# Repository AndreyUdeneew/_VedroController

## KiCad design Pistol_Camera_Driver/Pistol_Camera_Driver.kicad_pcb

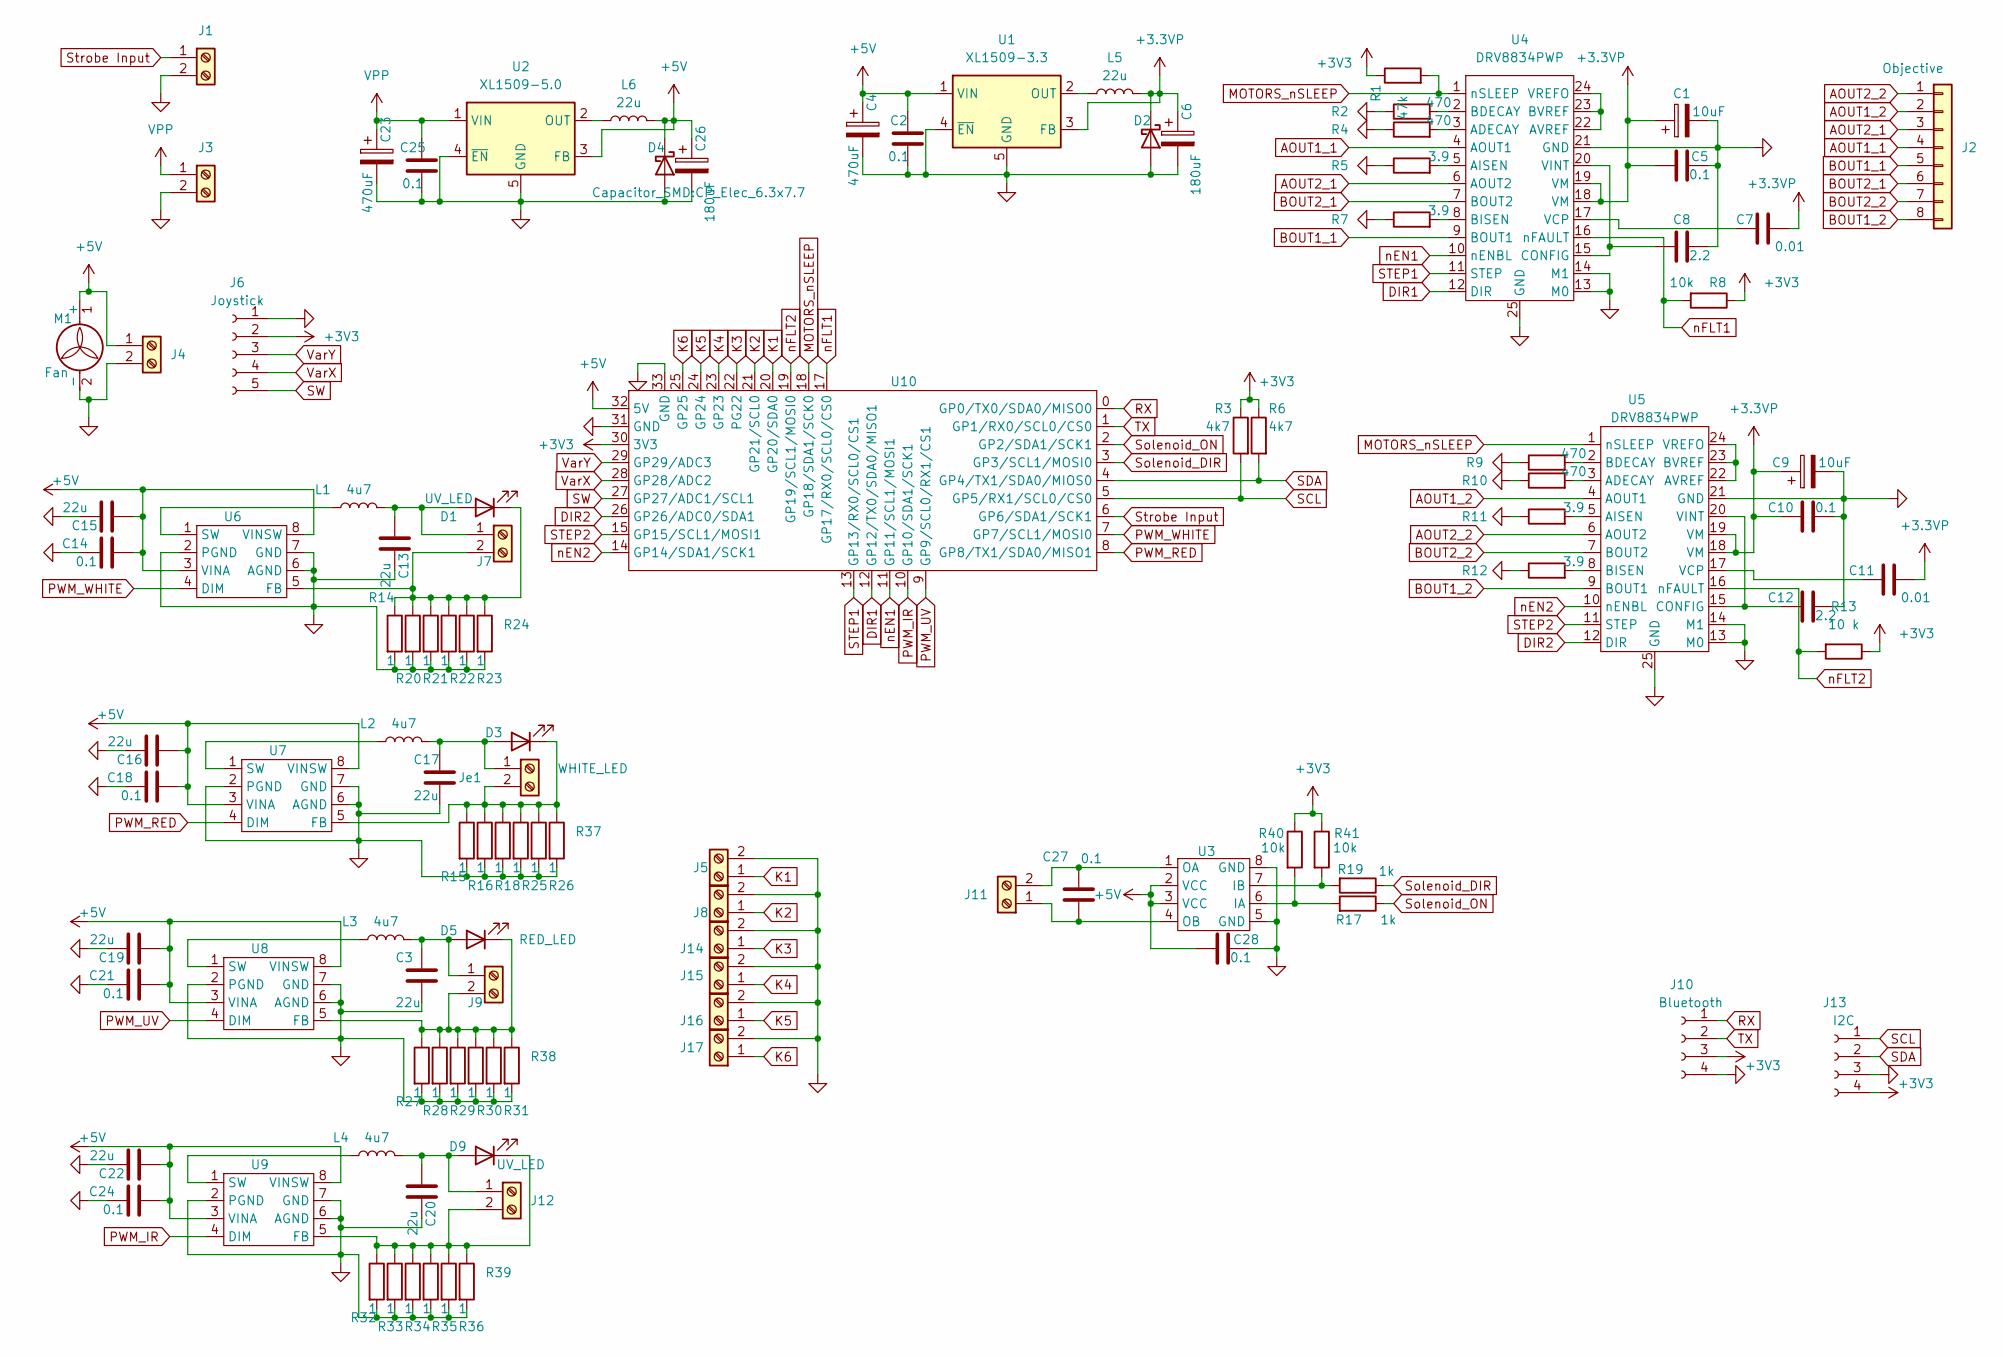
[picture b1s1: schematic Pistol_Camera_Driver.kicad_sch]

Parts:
C1, C9: 10uF; CP_Radial_D6.3mm_P2.50mm
C2, C5, C10, C14, C18, C21, C24, C25, C27, C28: 0.1; C_0603_1608Metric_Pad1.08x0.95mm_HandSolder
C3, C13, C15, C16, C17, C19, C20, C22: 22u; C_0603_1608Metric_Pad1.08x0.95mm_HandSolder
C4, C23: 470uF; CP_Elec_10x10.5
C6, C26: 180uF; CP_Elec_6.3x7.7
C7, C11: 0.01; C_0603_1608Metric_Pad1.08x0.95mm_HandSolder
C8, C12: 2.2; C_0603_1608Metric_Pad1.08x0.95mm_HandSolder
D1, D9: UV_LED
D2, D4: CDBA3100-HF; D_SMA
D3: WHITE_LED
D5: RED_LED
J1, J3, J4, J5, J7, J8, J9, J12, J14, J15, J16, J17: Screw_Terminal_01x02; PinSocket_1x02_P2.54mm_Vertical
J2: Objective; PinSocket_1x08_P1.27mm_Vertical
J6: Joystick; PinSocket_1x05_P2.54mm_Vertical
J10: Bluetooth; PinSocket_1x04_P2.54mm_Vertical
J11: Screw_Terminal_01x02; PinSocket_1x02_P1.27mm_Vertical
J13: I2C; PinSocket_1x04_P2.54mm_Vertical
Je1: Screw_Terminal_01x02; PinSocket_1x02_P2.54mm_Vertical
L1, L2, L3, L4: 4u7; L_Chilisin_BMRx00040412
L5, L6: 22u; L_Sunlord_SWPA4012S
M1: Fan
R1: 47k; R_0603_1608Metric_Pad0.98x0.95mm_HandSolder
R2, R4, R9, R10: 470; R_0603_1608Metric_Pad0.98x0.95mm_HandSolder
R3, R6: 4k7; R_0603_1608Metric_Pad0.98x0.95mm_HandSolder
R5, R7, R11, R12: 3.9; R_0603_1608Metric_Pad0.98x0.95mm_HandSolder
R8, R40, R41: 10k; R_0603_1608Metric_Pad0.98x0.95mm_HandSolder
R13: 10 k; R_0603_1608Metric_Pad0.98x0.95mm_HandSolder
R14, R15, R16, R18, R20, R21, R22, R23, R24, R25, R26, R27, R28, R29, R30, R31, R32, R33, R34, R35, R36, R37, R38, R39: 1; R_0603_1608Metric_Pad0.98x0.95mm_HandSolder
R17, R19: 1k; R_0603_1608Metric_Pad0.98x0.95mm_HandSolder
U1: XL1509-3.3; SOIC-8-1EP_3.9x4.9mm_P1.27mm_EP2.95x4.9mm_Mask2.71x3.4mm_Th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
U2: XL1509-5.0; SOIC-8-1EP_3.9x4.9mm_P1.27mm_EP2.95x4.9mm_Mask2.71x3.4mm_Th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
U3: SOIC-8_3.9x4.9mm_P1.27mm
U4, U5: DRV8834PWP
U6, U7, U8, U9: PowerIntegrations_SO-8
U10: RP2040Zero

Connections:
+3.3VP: C1.1, C5.2, C6.1, C7.2, C9.1, C10.1, C11.2, D2.1 (K), L5.2, U1.3 (FB), U4.18 (VM), U4.19 (VM), U5.18 (VM), U5.19 (VM)
+3V3: J6.2, J10.3, J13.4, R1.1, R3.1, R6.1, R8.1, R13.1, R40.1, R41.1, U10.30 (3V3)
+5V: C2.1, C4.1, C14.2, C15.1, C16.1, C18.2, C19.1, C21.2, C22.1, C24.2, C26.1, C28.2, D4.1 (K), J4.1, L6.2, M1.1 (+), U1.1 (VIN), U2.3 (FB), U3.2 (VCC), U3.3 (VCC), U6.3 (VINA), U6.8 (VINSW), U7.3 (VINA), U7.8 (VINSW), U8.3 (VINA), U8.8 (VINSW), U9.3 (VINA), U9.8 (VINSW), U10.32 (5V)
AOUT1_1: J2.4, U4.4 (AOUT1)
AOUT1_2: J2.2, U5.4 (AOUT1)
AOUT2_1: J2.3, U4.6 (AOUT2)
AOUT2_2: J2.1, U5.6 (AOUT2)
BOUT1_1: J2.5, U4.9 (BOUT1)
BOUT1_2: J2.8, U5.9 (BOUT1)
BOUT2_1: J2.6, U4.7 (BOUT2)
BOUT2_2: J2.7, U5.7 (BOUT2)
DIR1: U4.12 (DIR), U10.12 (GP12/TX0/SDA0/MISO1)
DIR2: U5.12 (DIR), U10.26 (GP26/ADC0/SDA1)
GND: C1.2, C2.2, C3.2, C4.2, C5.1, C6.2, C8.2, C9.2, C10.2, C12.2, C13.2, C14.1, C15.2, C16.2, C17.2, C18.1, C19.2, C20.2, C21.1, C22.2, C23.2, C24.1, C25.2, C26.2, C28.1, D2.2 (A), D4.2 (A), J1.2, J3.2, J4.2, J5.2, J6.1, J8.2, J10.4, J13.3, J14.2, J15.2, J16.2, J17.2, M1.2 (-), R2.1, R4.1, R5.1, R7.1, R9.1, R10.1, R11.1, R12.1, R14.2, R15.2, R16.2, R18.2, R20.2, R21.2, R22.2, R23.2, R24.2, R25.2, R26.2, R27.2, R28.2, R29.2, R30.2, R31.2, R32.2, R33.2, R34.2, R35.2, R36.2, R37.2, R38.2, R39.2, U1.4 (~EN), U1.5 (GND), U1.6 (GND), U1.7 (GND), U1.8 (GND), U1.9 (EP), U2.4 (~EN), U2.5 (GND), U2.6 (GND), U2.7 (GND), U2.8 (GND), U3.5 (GND), U3.8 (GND), U4.13 (M0), U4.14 (M1), U4.21 (GND), U4.25 (GND), U5.13 (M0), U5.14 (M1), U5.21 (GND), U5.25 (GND), U6.2 (PGND), U6.6 (AGND), U6.7 (GND), U7.2 (PGND), U7.6 (AGND), U7.7 (GND), U8.2 (PGND), U8.6 (AGND), U8.7 (GND), U9.2 (PGND), U9.6 (AGND), U9.7 (GND), U10.31 (GND), U10.33 (GND)
K1: J5.1, U10.20 (GP20/SDA0)
K2: J8.1, U10.21 (GP21/SCL0)
K3: J14.1, U10.22 (PG22)
K4: J15.1, U10.23 (GP23)
K5: J16.1, U10.24 (GP24)
K6: J17.1, U10.25 (GP25)
MOTORS_nSLEEP: R1.2, U4.1 (nSLEEP), U5.1 (nSLEEP), U10.18 (GP18/SDA1/SCK0)
unnamed: C13.1, D1.2 (A), J7.1, L1.2
unnamed: D1.1 (K), J7.2, R14.1, R20.1, R21.1, R22.1, R23.1, R24.1, U6.5 (FB)
unnamed: C3.1, D5.2 (A), J9.1, L3.2
unnamed: D5.1 (K), J9.2, R27.1, R28.1, R29.1, R30.1, R31.1, R38.1, U8.5 (FB)
unnamed: C27.2, J11.1, U3.4 (OB)
unnamed: C27.1, J11.2, U3.1 (OA)
unnamed: C20.1, D9.2 (A), J12.1, L4.2
unnamed: D9.1 (K), J12.2, R32.1, R33.1, R34.1, R35.1, R36.1, R39.1, U9.5 (FB)
unnamed: C17.1, D3.2 (A), Je1.1, L2.2
unnamed: D3.1 (K), Je1.2, R15.1, R16.1, R18.1, R25.1, R26.1, R37.1, U7.5 (FB)
unnamed: L5.1, U1.2 (OUT)
unnamed: L6.1, U2.2 (OUT)
unnamed: R17.2, R40.2, U3.6 (IA)
unnamed: R19.2, R41.2, U3.7 (IB)
unnamed: R4.2, U4.3 (ADECAY)
unnamed: R5.2, U4.5 (AISEN)
unnamed: U4.22 (AVREF), U4.23 (BVREF), U4.24 (VREFO)
unnamed: R2.2, U4.2 (BDECAY)
unnamed: R7.2, U4.8 (BISEN)
unnamed: C8.1, U4.15 (CONFIG), U4.20 (VINT)
unnamed: C7.1, U4.17 (VCP)
unnamed: R10.2, U5.3 (ADECAY)
unnamed: R11.2, U5.5 (AISEN)
unnamed: U5.22 (AVREF), U5.23 (BVREF), U5.24 (VREFO)
unnamed: R9.2, U5.2 (BDECAY)
unnamed: R12.2, U5.8 (BISEN)
unnamed: C12.1, U5.15 (CONFIG), U5.20 (VINT)
unnamed: C11.1, U5.17 (VCP)
unnamed: L1.1, U6.1 (SW)
unnamed: L2.1, U7.1 (SW)
unnamed: L3.1, U8.1 (SW)
unnamed: L4.1, U9.1 (SW)
PWM_IR: U9.4 (DIM), U10.10 (GP10/SDA1/SCK1)
PWM_RED: U7.4 (DIM), U10.8 (GP8/TX1/SDA0/MISO1)
PWM_UV: U8.4 (DIM), U10.9 (GP9/SCL0/RX1/CS1)
PWM_WHITE: U6.4 (DIM), U10.7 (GP7/SCL1/MOSI0)
RX: J10.1, U10.0 (GP0/TX0/SDA0/MISO0)
SCL: J13.1, R3.2, U10.5 (GP5/RX1/SCL0/CS0)
SDA: J13.2, R6.2, U10.4 (GP4/TX1/SDA0/MIOS0)
STEP1: U4.11 (STEP), U10.13 (GP13/RX0/SCL0/CS1)
STEP2: U5.11 (STEP), U10.15 (GP15/SCL1/MOSI1)
SW: J6.5, U10.27 (GP27/ADC1/SCL1)
Solenoid_DIR: R19.1, U10.3 (GP3/SCL1/MOSI0)
Solenoid_ON: R17.1, U10.2 (GP2/SDA1/SCK1)
Strobe Input: J1.1, U10.6 (GP6/SDA1/SCK1)
TX: J10.2, U10.1 (GP1/RX0/SCL0/CS0)
VPP: C23.1, C25.1, J3.1, U2.1 (VIN)
VarX: J6.4, U10.28 (GP28/ADC2)
VarY: J6.3, U10.29 (GP29/ADC3)
nEN1: U4.10 (nENBL), U10.11 (GP11/SCL1/MOSI1)
nEN2: U5.10 (nENBL), U10.14 (GP14/SDA1/SCK1)
nFLT1: R8.2, U4.16 (nFAULT), U10.17 (GP17/RX0/SCL0/CS0)
nFLT2: R13.2, U5.16 (nFAULT), U10.19 (GP19/SCL1/MOSI0)

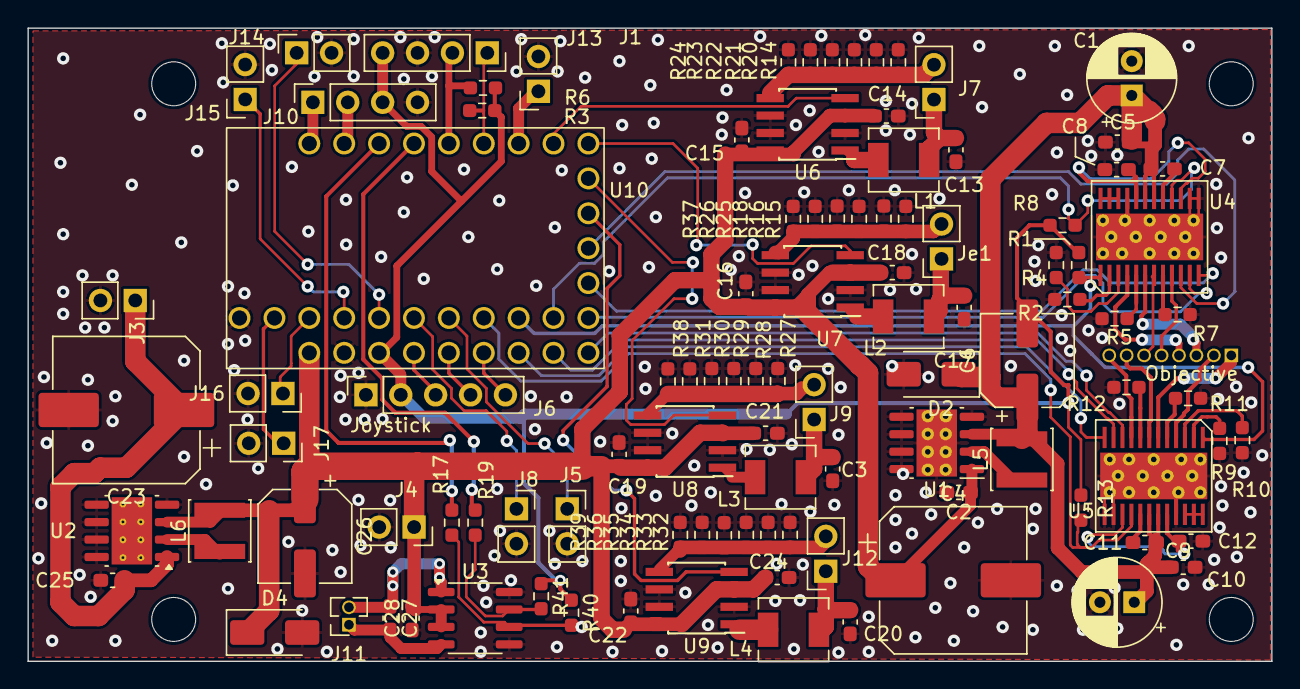
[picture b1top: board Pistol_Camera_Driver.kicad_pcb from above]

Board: 2 copper layers, 90.5 x 46.1 mm, 105 parts (1 on the bottom side), 74 nets.

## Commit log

2024-04-26 v0.1 RP2040 symbol, LED2000DR drivers were added
2024-04-29 V0.2 Seems 2B ready
2024-05-07 V0.3 Ordered
2024-07-30 v0.4 5 V DC/CD was added, Relay was changed to the H-bridge
